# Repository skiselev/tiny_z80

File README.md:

# Tiny Z80
Business Card Sized Zilog Z80 Single Board Computer

## Table of Content
* [Introduction](#introduction)
* [Specifications](#specifications)
* [Hardware Documentation](#hardware-documentation)
  * [Schematic and PCB Layout](#schematic-and-pcb-layout)
  * [Connectors and Jumpers](#connectors-and-jumpers)
  * [Bill of Materials](#bill-of-materials)
* [Firmware Documentation](#firmware-documentation)
  * [BIOS and OS](#bios-and-os)
  * [SPLD Fuse Map](#spld-fuse-map)
* [Release Notes](#release-notes)
  * [Changes](#changes)
  * [Known Issues](#known-issues)
  * [Wishlist](#wishlist)

## Introduction
Tiny Z80 is a business card sized (size?!) single board computer (SBC). It is mostly compatible with [Easy Z80](https://github.com/skiselev/easy_z80), and offers similar capabilities, including 512 KiB of battery-backed SRAM, 512 KiB Flash ROM, Z80 SIO and Z80 CTC (integrated in Z80 EIPC). Tiny Z80 includes a USB to Serial converter IC on board connected to one of the SIO ports, for ease of use with modern computers. The glue logic, including the memory paging registers is implemented using Altera MAX7000AE CPLD.

## Specifications
* Processor: Zilog Z80 EIPC - Z84C15, includes Z80 CPU, Z80 SIO, Z80 PIO, and Z80 CTC
* Memory: 512 KiB battery-backed SRAM, 512 KiB Flash ROM
* Input/Output:
  * Dual RS232 serial ports, implemented using Z80 SIO integrated into Z80 EIPC
  * FT231XS USB to Serial converter connected to SIO Port A
  * Two 8-bit parallel ports, implemented using Z80 PIO integrated into Z80 EIPC
  * User controllable LED
* Bus: [RC2014](https://rc2014.co.uk/) compatible
* Microprocessor Supervisor:
  * Reset generation
  * SRAM battery backup
  * Power failure NMI
  * Watchdog (optional)

## Hardware Documentation

### Schematic and PCB Layout

[Schematic - Version 1.0](KiCad/Tiny_Z80-Schematic-1.0.pdf)

[PCB Layout - Version 1.0](KiCad/Tiny_Z80-Board-1.0.pdf)

### Connectors and Jumpers

#### J1 - Serial_A - USB Serial
Pin  | Signal Name | Description
---- | ----------- | -----------
1    | VBUS        | Power Supply - +5V
2    | D-          | USB Data -
3    | D+          | USB Data +
4    | NC          | Not Connected
5    | GND         | Ground

#### J2 - Serial_B - FTDI Header - TTL Level
Pin  | Signal Name | Description
---- | ----------- | -----------
1    | GND         | Ground
2    | RTS         | RS232 / Request to Send
3    | VSER        | Power Supply - +5V (Optional, if F2 is installed)
4    | RXD         | RS232 / Receive
5    | TXD         | RS232 / Transmit
6    | CTS         | RS232 / Clear to Send

#### J3 - Parallel - PIO
Pin  | Signal Name | Description         | Pin  | Signal Name | Description
---- | ----------- | ------------------- | ---- | ----------- | -----------
1    | VCC         | Power Supply - +5V  | 2    | GND         | Ground
3    | PA0         | Port A - Data 0     | 4    | GND         | Ground
5    | PA1         | Port A - Data 1     | 6    | /BSTB       | Port B - Strobe 
7    | PA2         | Port A - Data 2     | 8    | BRDY        | Port B - Ready
9    | PA3         | Port A - Data 3     | 10   | PB7         | Port B - Data 7
11   | PA4         | Port A - Data 4     | 12   | PB6         | Port B - Data 6
13   | PA5         | Port A - Data 5     | 14   | PB5         | Port B - Data 5
15   | PA6         | Port A - Data 6     | 16   | PB4         | Port B - Data 4
17   | PA7         | Port A - Data 7     | 18   | PB3         | Port B - Data 3
19   | ARDY        | Port A - Ready      | 20   | PB2         | Port B - Data 2
21   | /ASTB       | Port A - Strobe     | 22   | PB1         | Port B - Data 1
23   | GND         | Ground              | 24   | PB0         | Port B - Data 0
25   | GND         | Ground              | 26   | VCC         | Power Supply - +5V

#### J4, J5, J6 - RC2014 Bus
Pin   | Signal Name | Description         | Pin  | Signal Name | Description
----- | ----------- | ------------------- | ---- | ----------- | -----------
J4-1  | A15         | Address A15; Output |      |             |
J4-2  | A14         | Address A14; Output |      |             |
J4-3  | A13         | Address A13; Output |      |             |
J4-4  | A12         | Address A12; Output |      |             |
J4-5  | A11         | Address A11; Output |      |             |
J4-6  | A10         | Address A10; Output |      |             |
J4-7  | A9          | Address A9; Output  |      |             |
J4-8  | A8          | Address A8; Output  |      |             |
J4-9  | A7          | Address A7; Output  |      |             |
J4-10 | A6          | Address A6; Output  |      |             |
J4-11 | A5          | Address A5; Output  |      |             |
J4-12 | A4          | Address A4; Output  |      |             |
J4-13 | A3          | Address A3; Output  |      |             |
J4-14 | A2          | Address A2; Output  |      |             |
J4-15 | A1          | Address A1; Output  |      |             |
J4-16 | A0          | Address A0; Output  |      |             |
J4-17 | GND         | Ground              | J5-1 | GND         | Ground
J4-18 | VCC         | Power Supply - +5V  | J5-2 | VCC         | Power Supply - +5V
J4-19 | /M1         | Machine Cycle One; Output | J5-3| /RFSH | DRAM refresh; Output
J4-20 | /RESET      | Reset; Output       | J5-4 | N/C         | Not connected
J4-21 | CPU_CLK     | CPU Clock; Output   | J5-5 | UART_CLK    | UART Clock (1.8432 MHz); Output
J4-22 | /INT        | Interrupt; Input    | J5-6 | /BUSACK     | DMA Bus Acknowledge; Output
J4-23 | /MREQ       | Memory Request; Output | J5-8 | /HALT    | Halt; Output
J4-24 | /WR         | Write Request; Output | J5-9 | /WAIT     | Wait; Input
J4-25 | /RD         | Read Request; Output | J5-10 | /NMI      | Non-maskable Interrupt; Input
J4-26 | /IORQ       | Input/Output Request; Output | |         |
J4-27 | D0          | Data D0; Input/Output |    |             |
J4-28 | D1          | Data D1; Input/Output |    |             |
J4-29 | D2          | Data D2; Input/Output |    |             |
J4-30 | D3          | Data D3; Input/Output |    |             |
J4-31 | D4          | Data D4; Input/Output |    |             |
J4-32 | D5          | Data D5; Input/Output |    |             |
J4-33 | D6          | Data D6; Input/Output |    |             |
J4-34 | D7          | Data D7; Input/Output |    |             |
J6-1  | TXDA        | Channel A, Transmit Data; Output | J6-2 | TXDB | Channel B, Transmit Data; Output
J6-3  | RXDA        | Channel A, Receive Data; Input   | J6-4 | RXDB | Channel B, Receive Data; Input
J6-5  | USR1        | User Pin 1, Not connected | J6-6 | USR5  | User Pin 5, Not connected 
J6-7  | IEI         | Interrupt Enable Input  | J6-8 | USR6    | User Pin 6, Not connected 
J6-9  | IEO         | Interrupt Enable Output | J6-10 | USR7    | User Pin 7, Not connected 

#### J7 - JTAG - CPLD
Pin  | Signal Name | Description      | Pin  | Signal Name | Description
---- | ----------- | ---------------- | ---- | ----------- | ----------------
1    | TCK         | Test Clock       | 2    | GND         | Ground
3    | TDO         | Test Data Output | 4    | 3.3V        | Power Supply - +3.3V
5    | TMS         | Test Mode Select | 6    | NC          | No Connect
7    | NC          | No Connect       | 8    | NC          | No Connect
9    | TDI         | Test Data Input  | 10   | GND         | Ground

#### JP1 - Serial Channel A Clock Select
Position        | Description
--------------- | -----------
*1-2 (default)* | 1.8432 MHz (115200 bps if using x16 mode)
2-3             | Programmable using CTC channel 0

#### JP2 - Serial Channel B Clock Select
Position        | Description
--------------- | -----------
*1-2 (default)* | 1.8432 MHz (115200 bps if using x16 mode)
2-3             | Programmable using CTC channel 1

#### JP3 - LDO Bypass
Solder instead of U7 LDO when using a 5V CPLD

#### JP4 - RAM_CS, JP5 - VRAM
Solder when not using U5 CPU Supervisor to connect RAM_CS and VCC directly to the SRAM IC

### Bill of Materials

#### Version 1.0

[Tiny Z80 project on Mouser.com](https://www.mouser.com/ProjectManager/ProjectDetail.aspx?AccessID=d29f509257) - View and order all components except of the PCB.

[Tiny Z80 project on OSH Park](https://oshpark.com/shared_projects/C0KRm6BH) - View and order the PCB.

Component type     | Reference | Description                                 | Quantity | Possible sources and notes 
------------------ | --------- | ------------------------------------------- | -------- | --------------------------
PCB                |           | Tiny Z80 PCB - Version 1.0                  | 1        | Order from a PCB manufacturer of your choice using provided Gerber or KiCad files
Battery Holder     | BT1       | CR2032 Keystone Electronics 534-1058        | 1        | Mouser [534-1058](https://www.mouser.com/ProductDetail/534-1058)
Battery            | BT1       | CR2032                                      | 1        | 
Capacitor          | C1 - C13  | 100nF 0603 SMT                              | 13       | Mouser [77-VJ0603Y104JXJPBC](https://www.mouser.com/ProductDetail/77-VJ0603Y104JXJPBC)
Capacitor          | C14, C15  | 33pF 0603 SMT                               | 2        | Mouser [77-VJ0603A330JXACBC](https://www.mouser.com/ProductDetail/77-VJ0603A330JXACBC)
Capacitor          | C16, C17  | 47pF 0603 SMT                               | 2        | Mouser [77-VJ0603A470JXACBC](https://www.mouser.com/ProductDetail/77-VJ0603A470JXACBC)
Capacitor          | C18       | 10nF	0603 SMT                               | 1        | Mouser [77-V0603Y103KXJAC31X](https://www.mouser.com/ProductDetail/77-V0603Y103KXJAC31X)
Capacitor          | C20, C19  | 10uF	1210 SMT                               | 2        | Mouser [581-TAJB106K020SNJ](https://www.mouser.com/ProductDetail/581-TAJB106K020SNJ)
Capacitor          | C21       | 47uF	SMT                                    | 1        | Mouser [581-TAJC476K016TNJ](https://www.mouser.com/ProductDetail/581-TAJC476K016TNJ)
LED                | D1        | 0603 SMT Power/Green                        | 1        | Mouser [78-VLMG1300-GS08](https://www.mouser.com/ProductDetail/78-VLMG1300-GS08)
LED                | D2        | 0603 SMT TX/Red                             | 1        | Mouser [78-VLMS1300-GS08](https://www.mouser.com/ProductDetail/78-VLMS1300-GS08), [78-VLMO1300-GS08](https://www.mouser.com/ProductDetail/78-VLMO1300-GS08)
LED                | D3        | 0603 SMT RX/Yellow                          | 1        | Mouser [78-VLMY1300-GS08](https://www.mouser.com/ProductDetail/78-VLMY1300-GS08)
LED                | D4        | 0603 SMT CPU/Blue                           | 1        | Mouser 
Polyfuse           | F2, F1    | 0.5A	SMT                                    | 2        | Mouser [650-MINISMDC050F-2](https://www.mouser.com/ProductDetail/650-MINISMDC050F-2) 
Connector          | J1        | Mini USB B                                  | 1        | Mouser [649-10118194-0001LF](https://www.mouser.com/ProductDetail/649-10118194-0001LF)
Connector          | J2        | Pin Header 1x6                              | 1        | 
Connector          | J3        | Pin Header 2x13                             | 1        | 
Connector          | J4, J5    | Pin Header 2x34, Right Angle                | 1        | Mouser [571-9-103326-0](https://www.mouser.com/ProductDetail/571-9-103326-0) Note: Cut to 34 pin, remove extra pins. Use remaining 2x6 piece for J6
Connector          | J6, J7    | Pin Header 2x5                              | 2        | 
Resistor           | R1, R2    | 27	Ohm 0603 SMT                             | 2        | Mouser [71-CRCW0603-27-E3](https://www.mouser.com/ProductDetail/71-CRCW0603-27-E3)
Resistor           | R3 - R6   | 1 kOhm 0603 SMT                             | 4        | Mouser [71-CRCW0603-1.0K-E3](https://www.mouser.com/ProductDetail/71-CRCW0603-1.0K-E3)
Resistor           | R7 - R18  | 4.7 kOhm	0603 SMT                           | 12       | Mouser [71-CRCW0603-4.7K-E3](https://www.mouser.com/ProductDetail/71-CRCW0603-4.7K-E3)
Resistor           | R19 - R25 | 10 kOhm 0603 SMT                            | 7        | Mouser [71-CRCW0603-10K-E3](https://www.mouser.com/ProductDetail/71-CRCW0603-10K-E3) 
Resistor           | R26       | 29.4 kOhm 0603 SMT                          | 1        | Mouser [71-CRCW0603-29.4K-E3](https://www.mouser.com/ProductDetail/71-CRCW0603-29.4K-E3)
Trimmer Resistor   | RV1       | 2 kOhm                                      | 1        | Mouser [652-TC33X-2-202E](https://www.mouser.com/ProductDetail/652-TC33X-2-202E), [81-PVG3G202C01R00](https://www.mouser.com/ProductDetail/81-PVG3G202C01R00)
Tactile Switch     | SW1       | Tactile Switch                              | 1        | Mouser [653-B3U-1000P](https://www.mouser.com/ProductDetail/653-B3U-1000P)
Integrated Circuit | U1        | Z84C15, Zilog Z80 EIPC, 16 MHz, QFP-100     | 1        | Mouser [692-Z84C1516FSG](https://www.mouser.com/ProductDetail/692-Z84C1516FSG)
Integrated Circuit | U2        | SST39SF040, 512 KiB Flash ROM, PLCC-32      | 1        | Mouser [579-39SF0405INHE](https://www.mouser.com/ProductDetail/579-39SF0405INHE)
Integrated Circuit | U3        | AS6C4008, 512 KiB SRAM, SOP-32              | 1        | Mouser [913-AS6C4008-55SIN](https://www.mouser.com/ProductDetail/913-AS6C4008-55SIN)
Integrated Circuit | U4        | EPM7064AETC44, Altera MAX 7000AE CPLD, TQFP-44 | 1        | Mouser [989-EPM7064AETC4410N](https://www.mouser.com/ProductDetail/989-EPM7064AETC4410N)
Integrated Circuit | U5        | MAX691xWE                                   | 1        | Mouser [584-ADM691AARWZ-R](https://www.mouser.com/ProductDetail/584-ADM691AARWZ-R)
Integrated Circuit | U6        | FT231XS                                     | 1        | Mouser [895-FT231XS-R](https://www.mouser.com/ProductDetail/895-FT231XS-R)
Integrated Circuit | U7        | TPS79333-EP                                 | 1        | Mouser [595-TPS79333DBVR](https://www.mouser.com/ProductDetail/595-TPS79333DBVR)
IC Socket          | U2        | PLCC32 SMD Socket                           | 1        | Mouser [649-69802-432LF](https://www.mouser.com/ProductDetail/649-69802-432LF)
Crystal Oscillator | X1        | 1.8432 MHz XO91                             | 1        | Mouser [559-F3345-184](https://www.mouser.com/ProductDetail/559-F3345-184)
Crystal Resonator  | Y1        | 16 MHz Crystal_GND24                        | 1        | Mouser [732-22516MF18X-G](https://www.mouser.com/ProductDetail/732-22516MF18X-G)

## Firmware Documentation

### BIOS and OS

Tiny Z80 is supported by [RomWBW](https://github.com/wwarthen/RomWBW) [v3.0.1](https://github.com/wwarthen/RomWBW/releases/tag/v3.0.1) and later. RomWBW includes BIOS, CP/M-80 2.2, Z-System, and a collection of utilities. It also should be possible to run [FUZIX](https://github.com/EtchedPixels/FUZIX) on this board.
*Note: Edit Easy Z80 configuration (cfg_ezz80.asm), set SIO0BASE to $18 and CTCBASE	to $10*

### CPLD Fuse Map

Tiny Z80 uses an Intel/Altera EPM7064AETC44 CPLD (U4) for address decode logic. The [CPLD fuse map](CPLD/tiny_z80.pof) and the CPLD source code are provided in [CPLD](CPLD) directory of this repository. Use free Altera Quartus II 13.0sp1 Web Edition to program the CPLD. Newer Quartus versions do not support Altera MAX7000 CPLDs.

## Release Notes

### Changes
* Version 1.0
  * Initial version

### Known Issues
* Version 1.0
  * Front silkscreen: J7 overlaps with 100nF value of C4
  
### Wishlist
* Version 1.0
  * None

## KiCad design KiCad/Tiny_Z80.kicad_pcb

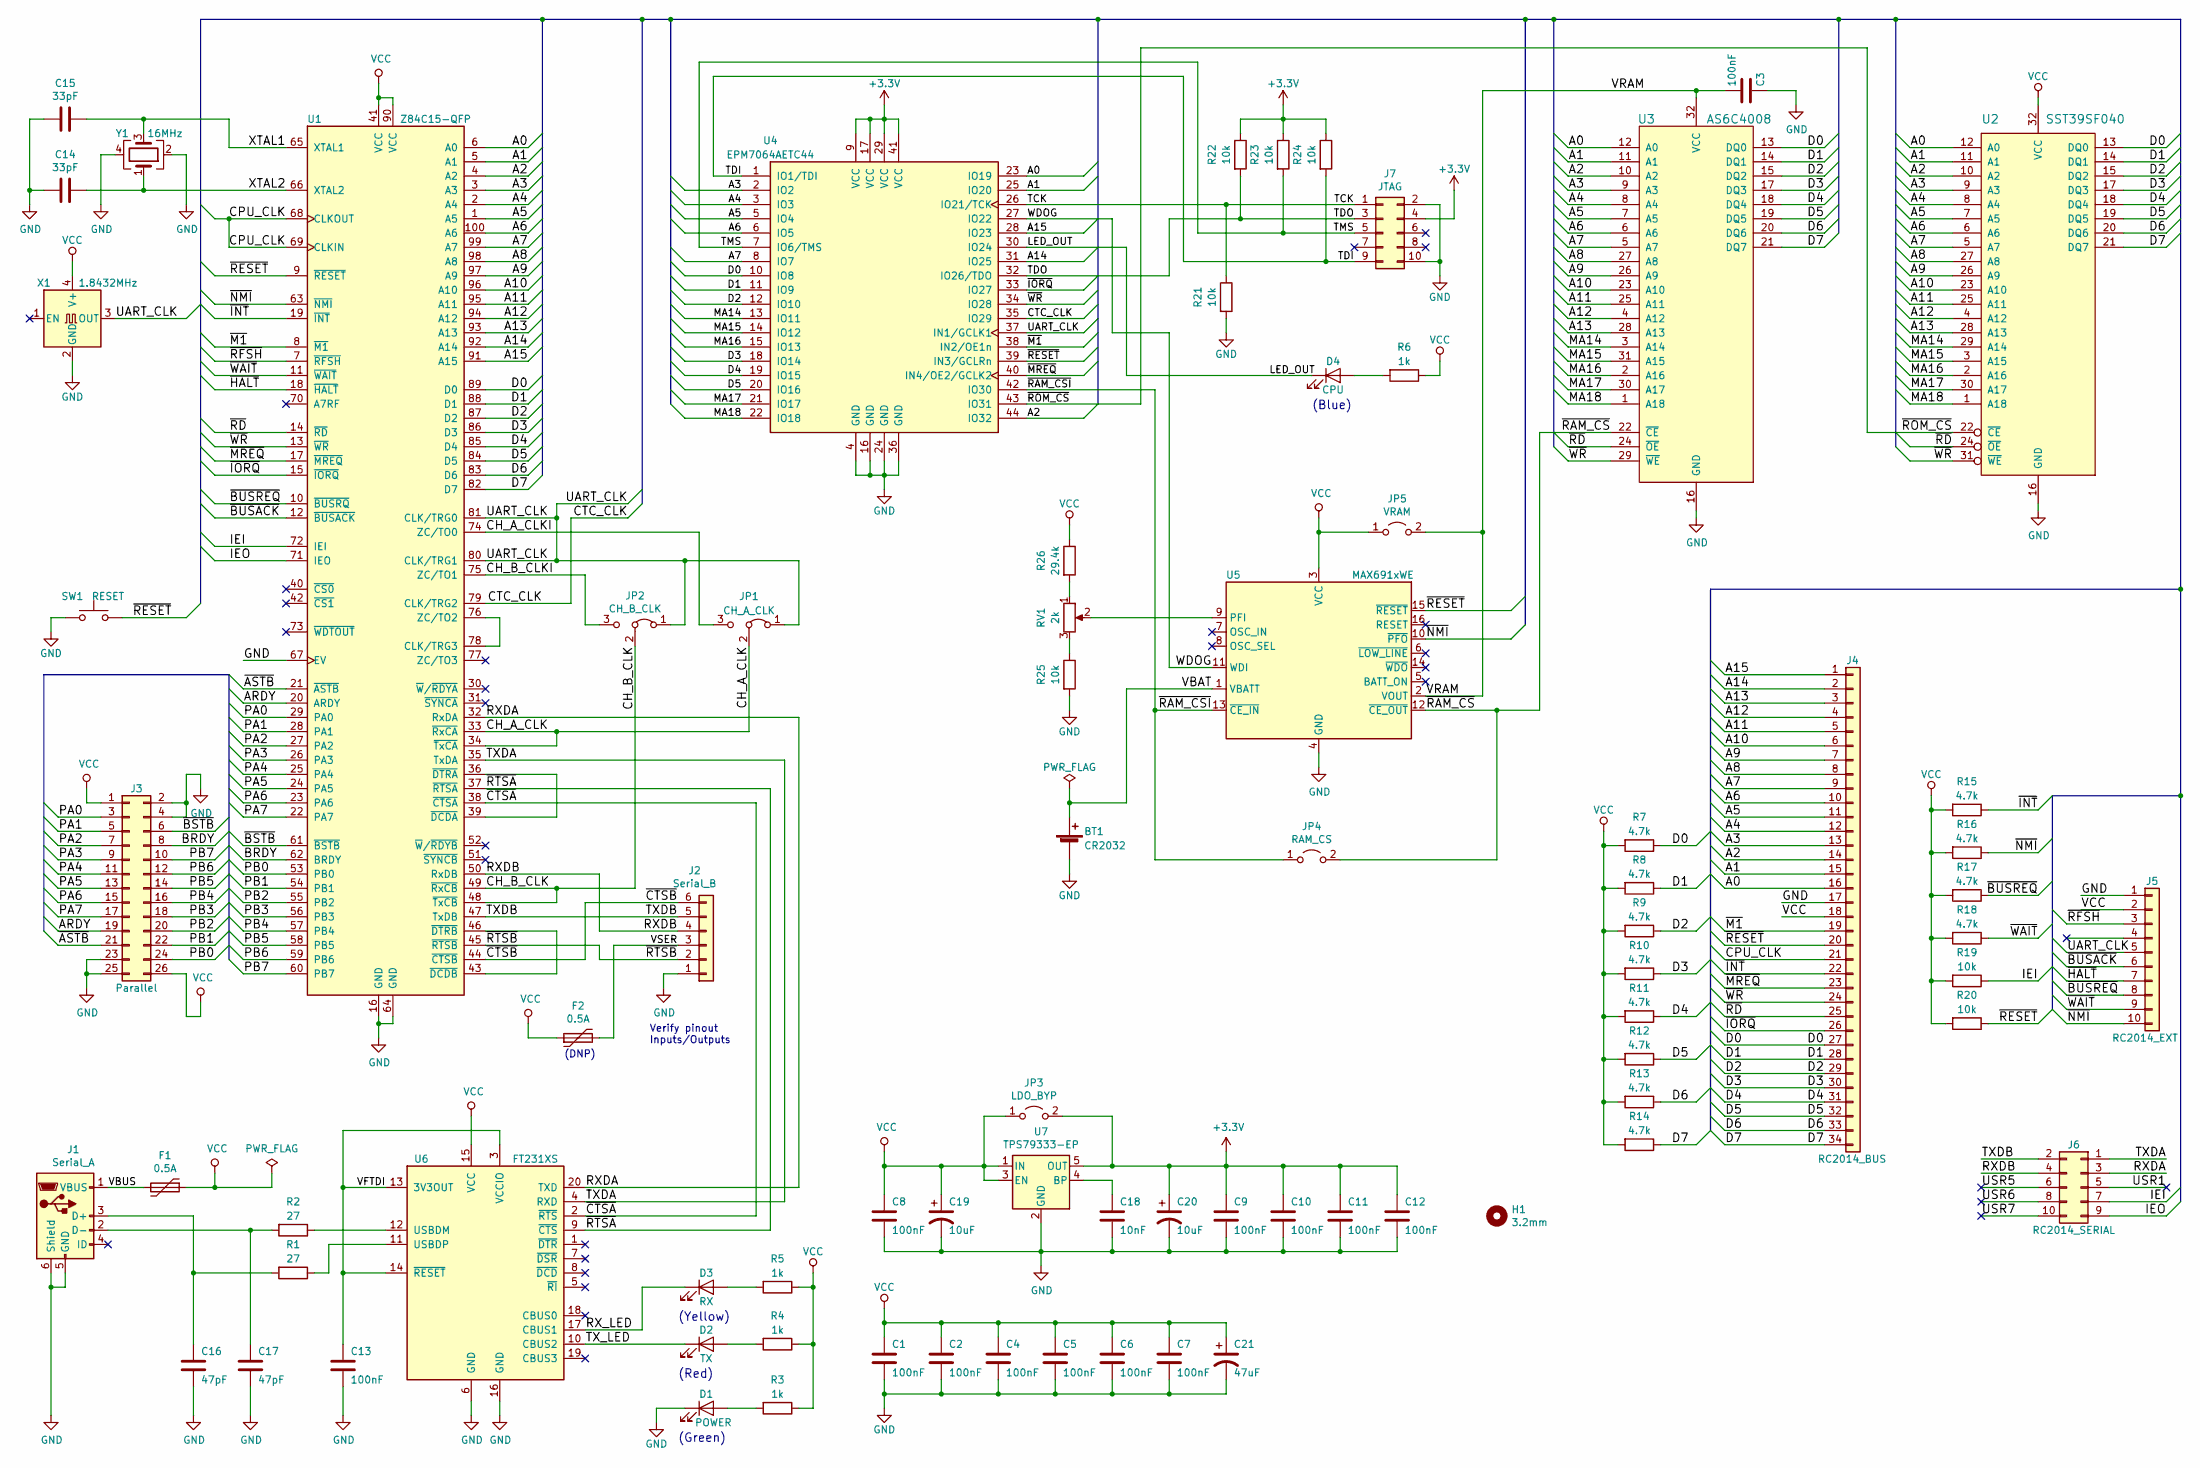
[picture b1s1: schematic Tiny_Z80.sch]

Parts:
BT1: CR2032; BatteryHolder_Keystone_1058_1x2032
C1, C2, C3, C4, C5, C6, C7, C8, C9, C10, C11, C12, C13: 100nF; C_0603_1608Metric_Pad1.05x0.95mm_HandSolder
C14, C15: 33pF; C_0603_1608Metric_Pad1.05x0.95mm_HandSolder
C16, C17: 47pF; C_0603_1608Metric_Pad1.05x0.95mm_HandSolder
C18: 10nF; C_0603_1608Metric_Pad1.05x0.95mm_HandSolder
C19, C20: 10uF; CP_EIA-6032-28_Kemet-C_Pad2.25x2.35mm_HandSolder
C21: 47uF; CP_EIA-6032-28_Kemet-C_Pad2.25x2.35mm_HandSolder
D1: POWER; LED_0603_1608Metric_Pad1.05x0.95mm_HandSolder
D2: TX; LED_0603_1608Metric_Pad1.05x0.95mm_HandSolder
D3: RX; LED_0603_1608Metric_Pad1.05x0.95mm_HandSolder
D4: CPU; LED_0603_1608Metric_Pad1.05x0.95mm_HandSolder
F1, F2: 0.5A; Fuse_1812_4532Metric_Pad1.30x3.40mm_HandSolder
H1: 3.2mm; MountingHole_3.2mm_M3_DIN965
J1: Serial_A; Conn_Micro_USB_B
J2: Serial_B; Conn_Pin_Header_6x1_2.54mm
J3: Parallel; Conn_Pin_Header_13x2_2.54mm
J4: RC2014_BUS; Conn_Pin_Header_34x1_2.54mm
J5: RC2014_EXT; Conn_Pin_Header_10x1_2.54mm
J6: RC2014_SERIAL; Conn_Pin_Header_5x2_2.54mm
J7: JTAG; Conn_Pin_Header_5x2_2.54mm
JP1: CH_A_CLK; SolderJumper-3_P1.3mm_Bridged12_RoundedPad1.0x1.5mm_NumberL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
JP2: CH_B_CLK; SolderJumper-3_P1.3mm_Bridged12_RoundedPad1.0x1.5mm_NumberL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
JP3: LDO_BYP; SolderJumper-2_P1.3mm_Open_RoundedPad1.0x1.5mm
JP4: RAM_CS; SolderJumper-2_P1.3mm_Open_RoundedPad1.0x1.5mm
JP5: VRAM; SolderJumper-2_P1.3mm_Open_RoundedPad1.0x1.5mm
R1, R2: 27; R_0603_1608Metric_Pad1.05x0.95mm_HandSolder
R3, R4, R5, R6: 1k; R_0603_1608Metric_Pad1.05x0.95mm_HandSolder
R7, R8, R9, R10, R11, R12, R13, R14, R15, R16, R17, R18: 4.7k; R_0603_1608Metric_Pad1.05x0.95mm_HandSolder
R19, R20, R21, R22, R23, R24, R25: 10k; R_0603_1608Metric_Pad1.05x0.95mm_HandSolder
R26: 29.4k; R_0603_1608Metric_Pad1.05x0.95mm_HandSolder
RV1: 2k; Potentiometer_Bourns_TC33X_Vertical
SW1: RESET; SW_SPST_B3U-1000P
U1: Z84C15-QFP; PQFP-100_14x20mm_P0.65mm
U2: SST39SF040; PLCC-32_SMD-Socket
U3: AS6C4008; SSOP-32_11.305x20.495mm_P1.27mm
U4: EPM7064AETC44; TQFP-44_10x10mm_P0.8mm
U5: MAX691xWE; SOIC-16W_7.5x10.3mm_P1.27mm
U6: FT231XS; SSOP-20_3.9x8.7mm_P0.635mm
U7: TPS79333-EP; SOT-23-5
X1: 1.8432MHz; Oscillator_SMD_EuroQuartz_XO91-4Pin_7.0x5.0mm_HandSoldering
Y1: 16MHz; Crystal_SMD_3225-4Pin_3.2x2.5mm_HandSoldering

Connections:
+3V3: C9.1, C10.1, C11.1, C12.1, C20.1, J7.4, JP3.2 (B), R22.1, R23.1, R24.1, U4.9 (VCC), U4.17 (VCC), U4.29 (VCC), U4.41 (VCC), U7.5 (OUT)
/A0: J4.16, U1.6 (A0), U2.12 (A0), U3.12 (A0), U4.23 (IO19)
/A1: J4.15, U1.5 (A1), U2.11 (A1), U3.11 (A1), U4.25 (IO20)
/A2: J4.14, U1.4 (A2), U2.10 (A2), U3.10 (A2), U4.44 (IO32)
/A3: J4.13, U1.3 (A3), U2.9 (A3), U3.9 (A3), U4.2 (IO2)
/A4: J4.12, U1.2 (A4), U2.8 (A4), U3.8 (A4), U4.3 (IO3)
/A5: J4.11, U1.1 (A5), U2.7 (A5), U3.7 (A5), U4.5 (IO4)
/A6: J4.10, U1.100 (A6), U2.6 (A6), U3.6 (A6), U4.6 (IO5)
/A7: J4.9, U1.99 (A7), U2.5 (A7), U3.5 (A7), U4.8 (IO7)
/A8: J4.8, U1.98 (A8), U2.27 (A8), U3.27 (A8)
/A9: J4.7, U1.97 (A9), U2.26 (A9), U3.26 (A9)
/A10: J4.6, U1.96 (A10), U2.23 (A10), U3.23 (A10)
/A11: J4.5, U1.95 (A11), U2.25 (A11), U3.25 (A11)
/A12: J4.4, U1.94 (A12), U2.4 (A12), U3.4 (A12)
/A13: J4.3, U1.93 (A13), U2.28 (A13), U3.28 (A13)
/A14: J4.2, U1.92 (A14), U4.31 (IO25)
/A15: J4.1, U1.91 (A15), U4.28 (IO23)
/ARDY: J3.19, U1.20 (ARDY)
/BRDY: J3.8, U1.62 (BRDY)
/CH_A_CLK: JP1.2 (C), U1.33 (~RxCA~), U1.34 (~TxCA~)
/CH_A_CLKI: JP1.3 (B), U1.74 (ZC/TO0)
/CH_B_CLK: JP2.2 (C), U1.48 (~TxCB~), U1.49 (~RxCB~)
/CH_B_CLKI: JP2.3 (B), U1.75 (ZC/TO1)
/CPU_CLK: J4.21, U1.68 (CLKOUT), U1.69 (CLKIN)
/CTC_CLK: U1.79 (CLK/TRG2), U4.35 (IO29)
/D0: J4.27, R7.1, U1.89 (D0), U2.13 (DQ0), U3.13 (DQ0), U4.10 (IO8)
/D1: J4.28, R8.1, U1.88 (D1), U2.14 (DQ1), U3.14 (DQ1), U4.11 (IO9)
/D2: J4.29, R9.1, U1.87 (D2), U2.15 (DQ2), U3.15 (DQ2), U4.12 (IO10)
/D3: J4.30, R10.1, U1.86 (D3), U2.17 (DQ3), U3.17 (DQ3), U4.18 (IO14)
/D4: J4.31, R11.1, U1.85 (D4), U2.18 (DQ4), U3.18 (DQ4), U4.19 (IO15)
/D5: J4.32, R12.1, U1.84 (D5), U2.19 (DQ5), U3.19 (DQ5), U4.20 (IO16)
/D6: J4.33, R13.1, U1.83 (D6), U2.20 (DQ6), U3.20 (DQ6)
/D7: J4.34, R14.1, U1.82 (D7), U2.21 (DQ7), U3.21 (DQ7)
/IEI: J6.7, R19.1, U1.72 (IEI)
/IEO: J6.9, U1.71 (IEO)
/LED_OUT: D4.1 (K), U4.30 (IO24)
/MA14: U2.29 (A14), U3.3 (A14), U4.13 (IO11)
/MA15: U2.3 (A15), U3.31 (A15), U4.14 (IO12)
/MA16: U2.2 (A16), U3.2 (A16), U4.15 (IO13)
/MA17: U2.30 (A17), U3.30 (A17), U4.21 (IO17)
/MA18: U2.1 (A18), U3.1 (A18), U4.22 (IO18)
/PA0: J3.3, U1.29 (PA0)
/PA1: J3.5, U1.28 (PA1)
/PA2: J3.7, U1.27 (PA2)
/PA3: J3.9, U1.26 (PA3)
/PA4: J3.11, U1.25 (PA4)
/PA5: J3.13, U1.24 (PA5)
/PA6: J3.15, U1.23 (PA6)
/PA7: J3.17, U1.22 (PA7)
/PB0: J3.24, U1.53 (PB0)
/PB1: J3.22, U1.54 (PB1)
/PB2: J3.20, U1.55 (PB2)
/PB3: J3.18, U1.56 (PB3)
/PB4: J3.16, U1.57 (PB4)
/PB5: J3.14, U1.58 (PB5)
/PB6: J3.12, U1.59 (PB6)
/PB7: J3.10, U1.60 (PB7)
/RXDA: J6.3, U1.32 (RxDA), U6.20 (TXD)
/RXDB: J2.4, J6.4, U1.50 (RxDB)
/RX_LED: D3.1 (K), U6.17 (CBUS1)
/TCK: J7.1, R21.1, U4.26 (IO21/TCK)
/TDI: J7.9, R24.2, U4.1 (IO1/TDI)
/TDO: J7.3, R22.2, U4.32 (IO26/TDO)
/TMS: J7.5, R23.2, U4.7 (IO6/TMS)
/TXDA: J6.1, U1.35 (TxDA), U6.4 (RXD)
/TXDB: J2.5, J6.2, U1.47 (TxDB)
/TX_LED: D2.1 (K), U6.10 (CBUS2)
/UART_CLK: J5.5, JP1.1 (A), JP2.1 (A), U1.80 (CLK/TRG1), U1.81 (CLK/TRG0), U4.37 (IN1/GCLK1), X1.3 (OUT)
/USR1: J6.5
/USR5: J6.6
/USR6: J6.8
/USR7: J6.10
/VBAT: BT1.1 (+), U5.1 (VBATT)
/VBUS: F1.2, J1.1 (VBUS)
/VFTDI: C13.1, U6.3 (VCCIO), U6.13 (3V3OUT), U6.14 (~RESET)
/VRAM: C3.2, JP5.2 (B), U3.32 (VCC), U5.2 (VOUT)
/VSER: F2.2, J2.3
/WDOG: U4.27 (IO22), U5.11 (WDI)
/XTAL1: C15.1, U1.65 (XTAL1), Y1.3
/XTAL2: C14.1, U1.66 (XTAL2), Y1.1
/~ASTB~: J3.21, U1.21 (~ASTB~)
/~BSTB~: J3.6, U1.61 (~BSTB~)
/~BUSACK: J5.6, U1.12 (~BUSACK~)
/~BUSREQ: J5.8, R17.1, U1.10 (~BUSRQ~)
/~CTSA: U1.38 (~CTSA~), U6.2 (~RTS)
/~CTSB: J2.6, U1.44 (~CTSB~)
/~HALT: J5.7, U1.18 (~HALT~)
/~INT: J4.22, R15.1, U1.19 (~INT~)
/~IORQ: J4.26, U1.15 (~IORQ~), U4.33 (IO27)
/~M1: J4.19, U1.8 (~M1~), U4.38 (IN2/OE1n)
/~MREQ: J4.23, U1.17 (~MREQ~), U4.40 (IN4/OE2/GCLK2)
/~NMI: J5.10, R16.1, U1.63 (~NMI~), U5.10 (~PFO)
/~RAM_CS: JP4.2 (B), U3.22 (~CE), U5.12 (~CE_OUT)
/~RAM_CSI: JP4.1 (A), U4.42 (IO30), U5.13 (~CE_IN)
/~RD: J4.25, U1.14 (~RD~), U2.24 (~OE), U3.24 (~OE)
/~RESET: J4.20, R20.1, SW1.1, U1.9 (~RESET~), U4.39 (IN3/GCLRn), U5.15 (~RESET)
/~RFSH: J5.3, U1.7 (~RFSH~)
/~ROM_CS: U2.22 (~CE), U4.43 (IO31)
/~RTSA: U1.37 (~RTSA~), U6.9 (~CTS)
/~RTSB: J2.2, U1.45 (~RTSB~)
/~WAIT: J5.9, R18.1, U1.11 (~WAIT~)
/~WR: J4.24, U1.13 (~WR~), U2.31 (~WE), U3.29 (~WE), U4.34 (IO28)
GND: BT1.2 (-), C1.2, C2.2, C3.1, C4.2, C5.2, C6.2, C7.2, C8.2, C9.2, C10.2, C11.2, C12.2, C13.2, C14.2, C15.2, C16.2, C17.2, C18.2, C19.2, C20.2, C21.2, D1.1 (K), J1.5 (GND), J1.6 (Shield), J2.1, J3.2, J3.4, J3.23, J3.25, J4.17, J5.1, J7.2, J7.10, R21.2, R25.2, SW1.2, U1.16 (GND), U1.64 (GND), U1.67 (EV), U2.16 (GND), U3.16 (GND), U4.4 (GND), U4.16 (GND), U4.24 (GND), U4.36 (GND), U5.4 (GND), U6.6 (GND), U6.16 (GND), U7.2 (GND), X1.2 (GND), Y1.2, Y1.4
unnamed: C16.1, J1.3 (D+), R1.2
unnamed: C17.1, J1.2 (D-), R2.2
unnamed: C18.1, U7.4 (BP)
unnamed: D1.2 (A), R3.2
unnamed: D2.2 (A), R4.2
unnamed: D3.2 (A), R5.2
unnamed: D4.2 (A), R6.2
unnamed: R1.1, U6.11 (USBDP)
unnamed: R2.1, U6.12 (USBDM)
unnamed: R25.1, RV1.3
unnamed: R26.2, RV1.1
unnamed: RV1.2, U5.9 (PFI)
unnamed: U1.36 (~DTRA~), U1.39 (~DCDA~)
unnamed: U1.43 (~DCDB~), U1.46 (~DTRB~)
unnamed: U1.76 (ZC/TO2), U1.78 (CLK/TRG3)
VCC: C1.1, C2.1, C4.1, C5.1, C6.1, C7.1, C8.1, C19.1, C21.1, F1.1, F2.1, J3.1, J3.26, J4.18, J5.2, JP3.1 (A), JP5.1 (A), R3.1, R4.1, R5.1, R6.1, R7.2, R8.2, R9.2, R10.2, R11.2, R12.2, R13.2, R14.2, R15.2, R16.2, R17.2, R18.2, R19.2, R20.2, R26.1, U1.41 (VCC), U1.90 (VCC), U2.32 (VCC), U5.3 (VCC), U6.15 (VCC), U7.1 (IN), U7.3 (EN), X1.4 (V+)

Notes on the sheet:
Verify pinout Inputs/Outputs
(DNP)
(Yellow)
(Red)
(Green)
(Blue)

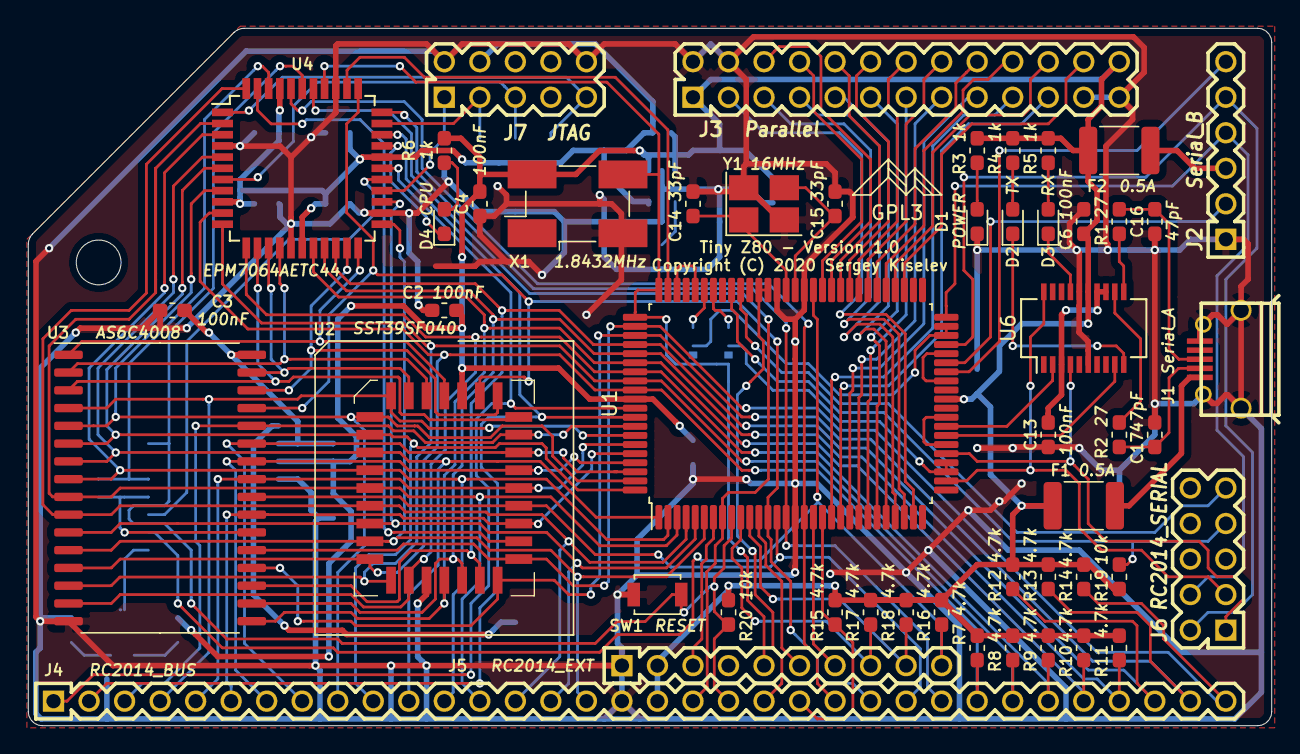
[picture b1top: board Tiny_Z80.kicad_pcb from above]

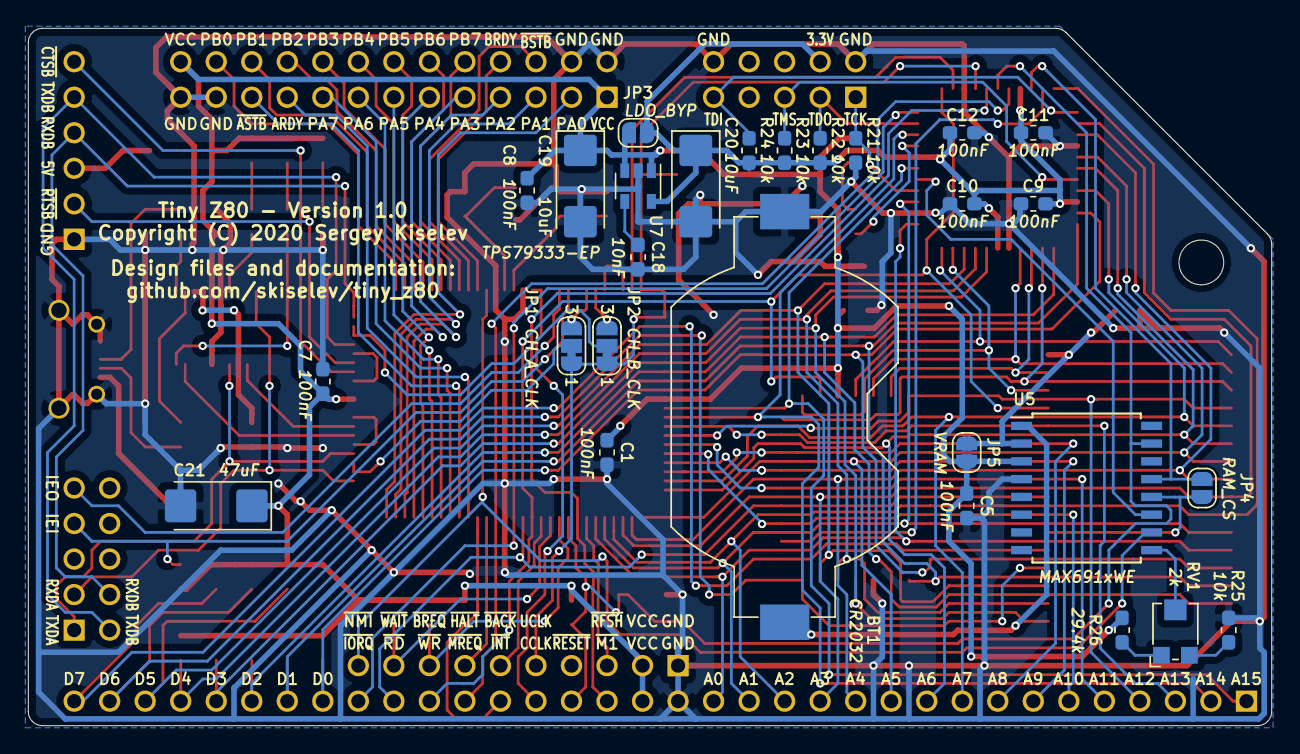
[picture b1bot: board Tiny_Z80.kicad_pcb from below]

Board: 2 copper layers, 88.9 x 49.9 mm, 78 parts (27 on the bottom side), 115 nets.

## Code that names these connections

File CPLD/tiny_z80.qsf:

# -------------------------------------------------------------------------- #
#
# Copyright (C) 1991-2012 Altera Corporation
# Your use of Altera Corporation's design tools, logic functions 
# and other software and tools, and its AMPP partner logic 
# functions, and any output files from any of the foregoing 
# (including device programming or simulation files), and any 
# associated documentation or information are expressly subject 
# to the terms and conditions of the Altera Program License 
# Subscription Agreement, Altera MegaCore Function License 
# Agreement, or other applicable license agreement, including, 
# without limitation, that your use is for the sole purpose of 
# programming logic devices manufactured by Altera and sold by 
# Altera or its authorized distributors.  Please refer to the 
# applicable agreement for further details.
#
# -------------------------------------------------------------------------- #
#
# Quartus II 32-bit
# Version 12.0 Build 178 05/31/2012 SJ Web Edition
# Date created = 16:51:09  September 12, 2019
#
# -------------------------------------------------------------------------- #
#
# Notes:
#
# 1) The default values for assignments are stored in the file:
#		tiny_z80_assignment_defaults.qdf
#    If this file doesn't exist, see file:
#		assignment_defaults.qdf
#
# 2) Altera recommends that you do not modify this file. This
#    file is updated automatically by the Quartus II software
#    and any changes you make may be lost or overwritten.
#
# -------------------------------------------------------------------------- #


set_global_assignment -name FAMILY MAX7000AE
set_global_assignment -name DEVICE "EPM7064AETC44-10"
set_global_assignment -name TOP_LEVEL_ENTITY tiny_z80
set_global_assignment -name ORIGINAL_QUARTUS_VERSION 12.0
set_global_assignment -name PROJECT_CREATION_TIME_DATE "16:51:09  SEPTEMBER 12, 2019"
set_global_assignment -name LAST_QUARTUS_VERSION "13.0 SP1"
set_global_assignment -name ERROR_CHECK_FREQUENCY_DIVISOR "-1"
set_global_assignment -name MIN_CORE_JUNCTION_TEMP 0
set_global_assignment -name MAX_CORE_JUNCTION_TEMP 85
set_global_assignment -name EDA_SIMULATION_TOOL "ModelSim-Altera (VHDL)"
set_global_assignment -name EDA_OUTPUT_DATA_FORMAT VHDL -section_id eda_simulation
set_global_assignment -name VHDL_FILE tiny_z80_vhdl.vhd
set_global_assignment -name VHDL_FILE page_reg_4x6.vhd
set_global_assignment -name VHDL_FILE d_ff_rst_vhdl.vhd
set_global_assignment -name QIP_FILE page_reg_4x6_lpm.qip
set_global_assignment -name MAX7000_DEVICE_IO_STANDARD "3.3-V LVCMOS"
set_global_assignment -name USE_CONFIGURATION_DEVICE ON
set_location_assignment PIN_37 -to UART_CLK
set_location_assignment PIN_1 -to TDI
set_location_assignment PIN_38 -to M1
set_location_assignment PIN_44 -to A[2]
set_location_assignment PIN_34 -to WR
set_location_assignment PIN_7 -to TMS
set_location_assignment PIN_14 -to MA[15]
set_location_assignment PIN_8 -to A[7]
set_location_assignment PIN_11 -to D[1]
set_location_assignment PIN_3 -to A[4]
set_location_assignment PIN_35 -to CTC_CLK
set_location_assignment PIN_23 -to A[0]
set_location_assignment PIN_31 -to A_HI[14]
set_location_assignment PIN_21 -to MA[17]
set_location_assignment PIN_22 -to MA[18]
set_location_assignment PIN_25 -to A[1]
set_location_assignment PIN_12 -to D[2]
set_location_assignment PIN_19 -to D[4]
set_location_assignment PIN_6 -to A[6]
set_location_assignment PIN_5 -to A[5]
set_location_assignment PIN_26 -to TCK
set_location_assignment PIN_40 -to MREQ
set_location_assignment PIN_33 -to IORQ
set_location_assignment PIN_10 -to D[0]
set_location_assignment PIN_28 -to A_HI[15]
set_location_assignment PIN_32 -to TDO
set_location_assignment PIN_18 -to D[3]
set_location_assignment PIN_20 -to D[5]
set_location_assignment PIN_15 -to MA[16]
set_location_assignment PIN_39 -to RSTn
set_location_assignment PIN_2 -to A[3]
set_location_assignment PIN_13 -to MA[14]
set_location_assignment PIN_42 -to RAM_CSn
set_location_assignment PIN_43 -to ROM_CSn

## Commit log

2020-07-09 Add KiCad files and images
2020-07-11 Add CPLD files
2020-07-11 README: Update CPLD files location
2020-07-11 CPLD: formatting
2020-07-11 CPLD: Add watchdog version
2020-07-14 README: Add connectors and jumpers documentation
2020-07-20 README: Add J4/J5/J6 part
2020-07-20 Move J7 reference so it does not overlap with 100nF value of C4
2020-07-20 Add Gerber files
2020-08-07 README: Typo fix

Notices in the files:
KiCad/Tiny_Z80.kicad_pcb:
Copyright (C) 2020 Sergey Kiselev
GPL3
